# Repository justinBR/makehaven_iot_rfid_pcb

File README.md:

# makehaven_iot_rfid_pcb
connects together the components of the makehaven iot/rfid system

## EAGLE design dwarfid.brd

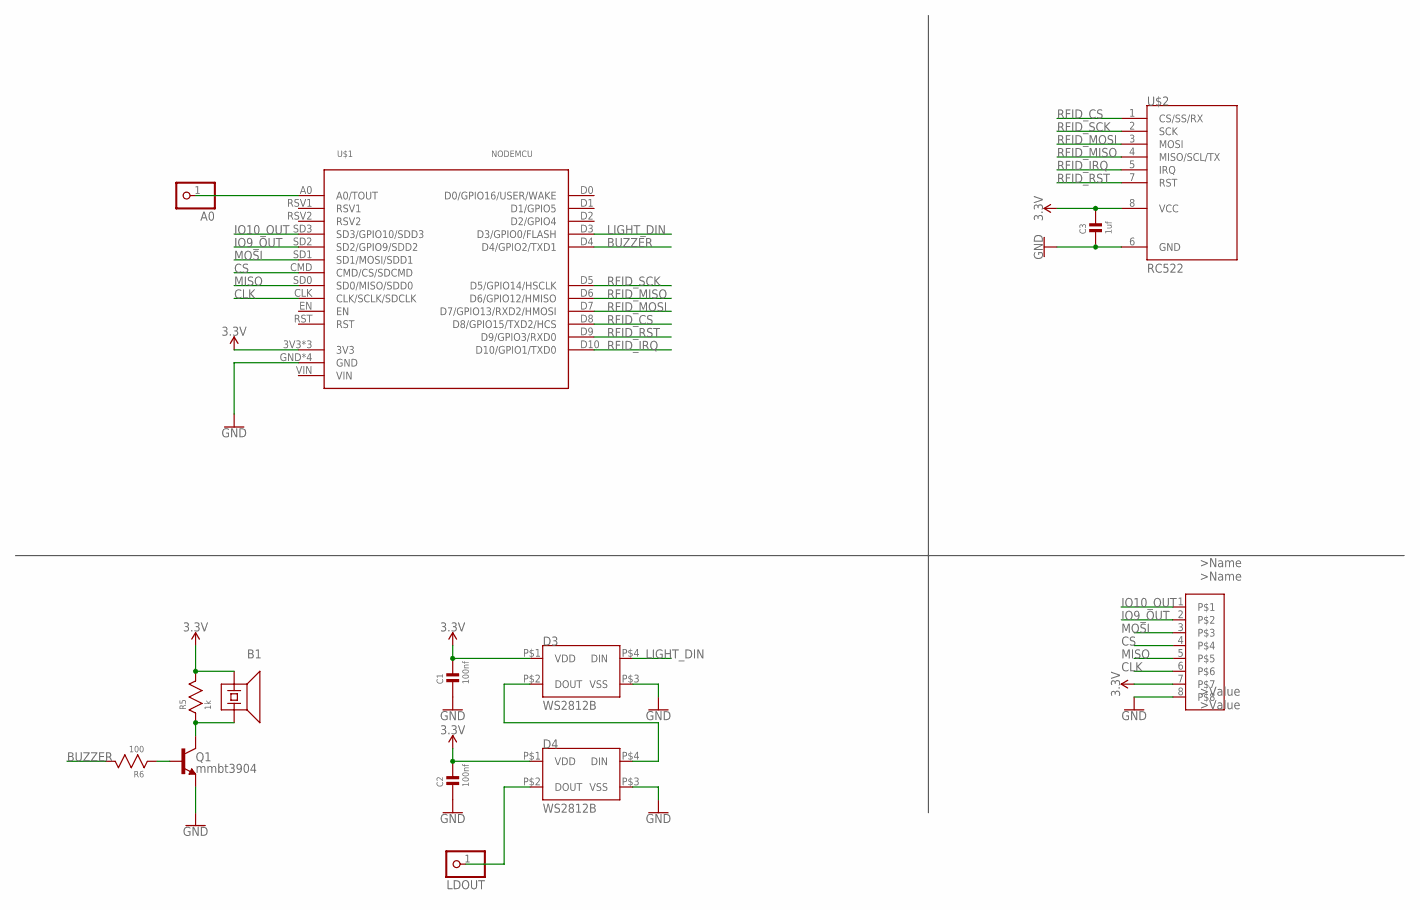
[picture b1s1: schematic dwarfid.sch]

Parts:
A0: PINHD-1X1; 1X01
B1: PS1720P02_PIEZO_BUZZER; PS1720P02_PIEZO
C1, C2: 100nf; PASSIVE_0603
C3: 1uf; PASSIVE_0603
D3, D4: WS2812B
LDOUT: PINHD-1X1; 1X01
Q1: mmbt3904; SOT23-3
R5: 1k; PASSIVE_0603
R6: 100; PASSIVE_0603
U$1: NODEMCU
U$2: RC522
U$3: JST8_2MM_RIGHTANGLE; JST_2MM_8POS

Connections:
3.3V: B1.P$1, C1.P$2, C2.P$2, C3.P$2, D3.P$1 (VDD), D4.P$1 (VDD), R5.P$2, U$1.3V3, U$1.3V3_2 (3V3), U$1.3V3_3 (3V3), U$2.8 (VCC), U$3.7
BUZZER: R6.P$2, U$1.D4 (D4/GPIO2/TXD1)
CLK: U$1.CLK (CLK/SCLK/SDCLK), U$3.6
CS: U$1.CMD (CMD/CS/SDCMD), U$3.4
GND: C1.P$1, C2.P$1, C3.P$1, D3.P$3 (VSS), D4.P$3 (VSS), Q1.2 (E), U$1.GND, U$1.GND2 (GND), U$1.GND3 (GND), U$1.GND4 (GND), U$2.6 (GND), U$3.8
IO9_OUT: U$1.SD2 (SD2/GPIO9/SDD2), U$3.2
IO10_OUT: U$1.SD3 (SD3/GPIO10/SDD3), U$3.1
LIGHT_DIN: D3.P$4 (DIN), U$1.D3 (D3/GPIO0/FLASH)
MISO: U$1.SD0 (SD0/MISO/SDD0), U$3.5
MOSI: U$1.SD1 (SD1/MOSI/SDD1), U$3.3
unnamed: D4.P$2 (DOUT), LDOUT.1
unnamed: B1.P$2, Q1.3 (C), R5.P$1
unnamed: D3.P$2 (DOUT), D4.P$4 (DIN)
unnamed: A0.1, U$1.A0 (A0/TOUT)
unnamed: Q1.1 (B), R6.P$1
RFID_CS: U$1.D8 (D8/GPIO15/TXD2/HCS), U$2.1 (CS/SS/RX)
RFID_IRQ: U$1.D10 (D10/GPIO1/TXD0), U$2.5 (IRQ)
RFID_MISO: U$1.D6 (D6/GPIO12/HMISO), U$2.4 (MISO/SCL/TX)
RFID_MOSI: U$1.D7 (D7/GPIO13/RXD2/HMOSI), U$2.3 (MOSI)
RFID_RST: U$1.D9 (D9/GPIO3/RXD0), U$2.7 (RST)
RFID_SCK: U$1.D5 (D5/GPIO14/HSCLK), U$2.2 (SCK)

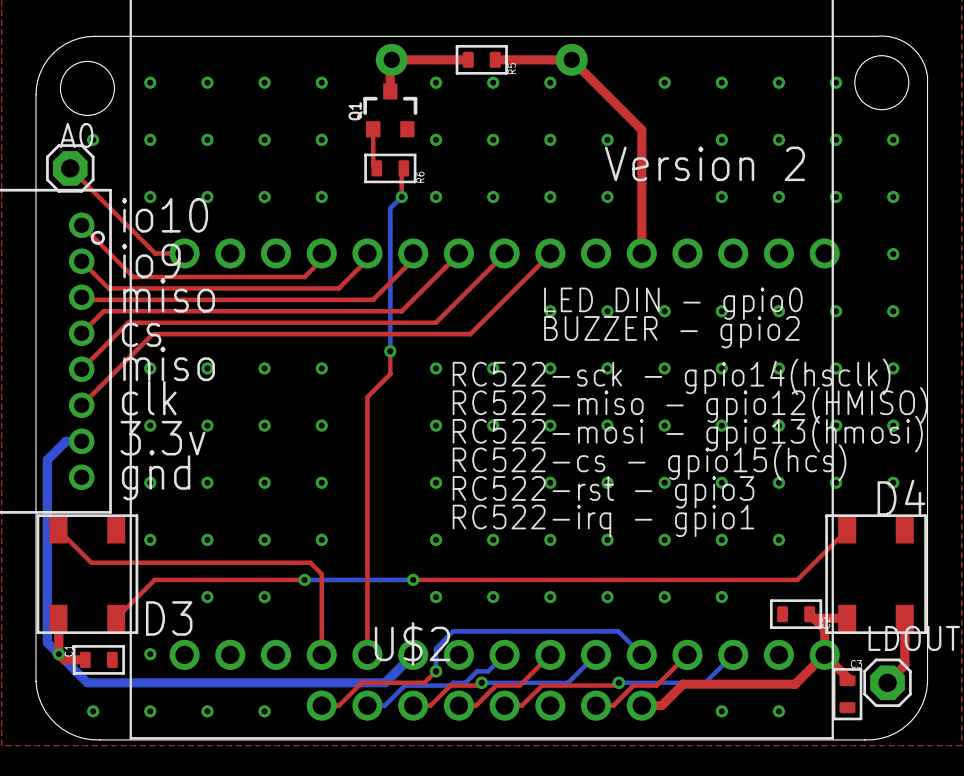
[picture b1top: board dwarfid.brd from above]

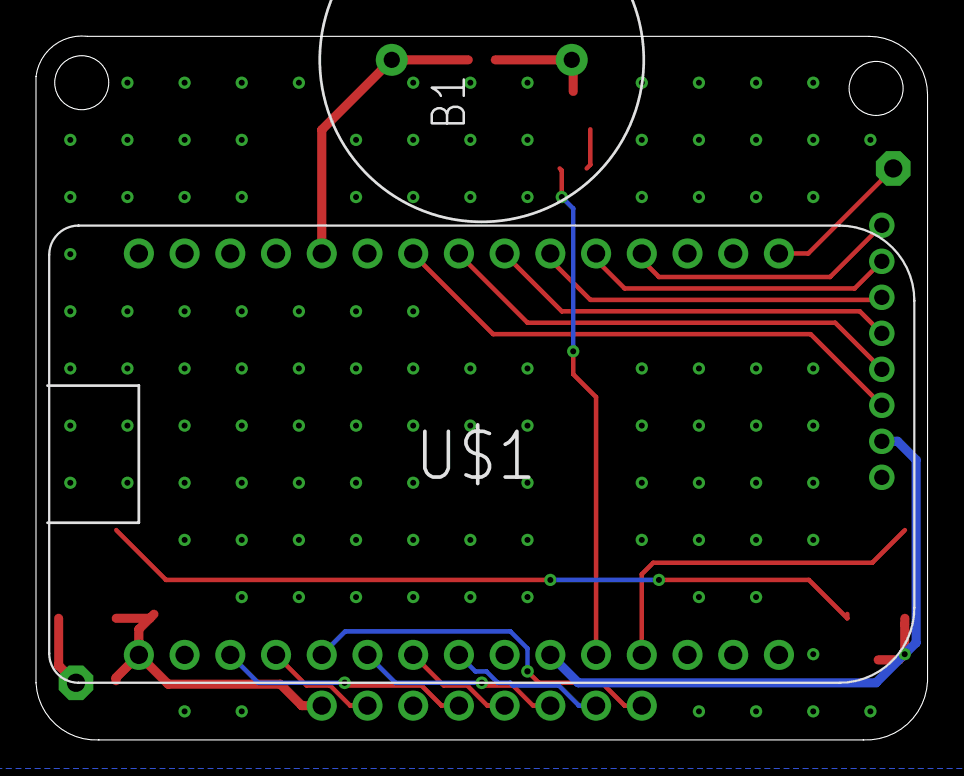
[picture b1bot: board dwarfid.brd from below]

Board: 2 copper layers, 49.5 x 39.1 mm, 14 parts (2 on the bottom side), 21 nets.

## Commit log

2017-09-24 initial commit of makehaven iot rfid boards
2017-09-24 added some images so that people without eagle can see the design at a glance.
2017-09-24 Create README.md
    Eagle pcb design files for makehaven card reader system.
    pins used for rc522:
    rfid_cs: gpio16
    rfid_sck: gpio5
    rfid_mosi: gpio4
    rfid_flash: gpio0
2017-10-27 fixed the spacing for the nodeMCU pins
    moved the LEDs to the bottom of the display
    Changed the current setting resistor for both the LEDs and the buzzer to 100 ohms.
    remapped the rfid card reader to use pins that can also be used as hardware spi pins.
    Put both the buzzer and the LEDs on pwm compatible pins
    replaced the 6pin jst connector with an 8pin connector.
    added the other hardware spi pins to the jst connector.
2017-11-04 minor intermediate changed before switching out the LEDs for
2017-11-04 replaced the LEDs with WS2812Bs.
    Moved the rfid board down so that it will be easier to solder.
    unfortunately both of these changes required us to increase the size of the board.
2017-11-04 Moved the board up so that the bottom line is at y=0
2017-11-04 fixed a overlap error cause by moving the nodeMCU back a bit.
2017-11-04 fixed some weird errors in the silk screen that I think were caused by accidentally pulling from fusion360 earlier.
2017-11-04 added a version number

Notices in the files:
parts and their libraries:
SparkFun-DiscreteSemi: Licensing: Creative Commons ShareAlike 4.0 International - https://creativecommons.org/licenses/by-sa/4.0
